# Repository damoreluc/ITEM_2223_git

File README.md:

# ITEM_2223_git
Repository progetti hardware con Autodesk Eagle di ITEM 2022-2023

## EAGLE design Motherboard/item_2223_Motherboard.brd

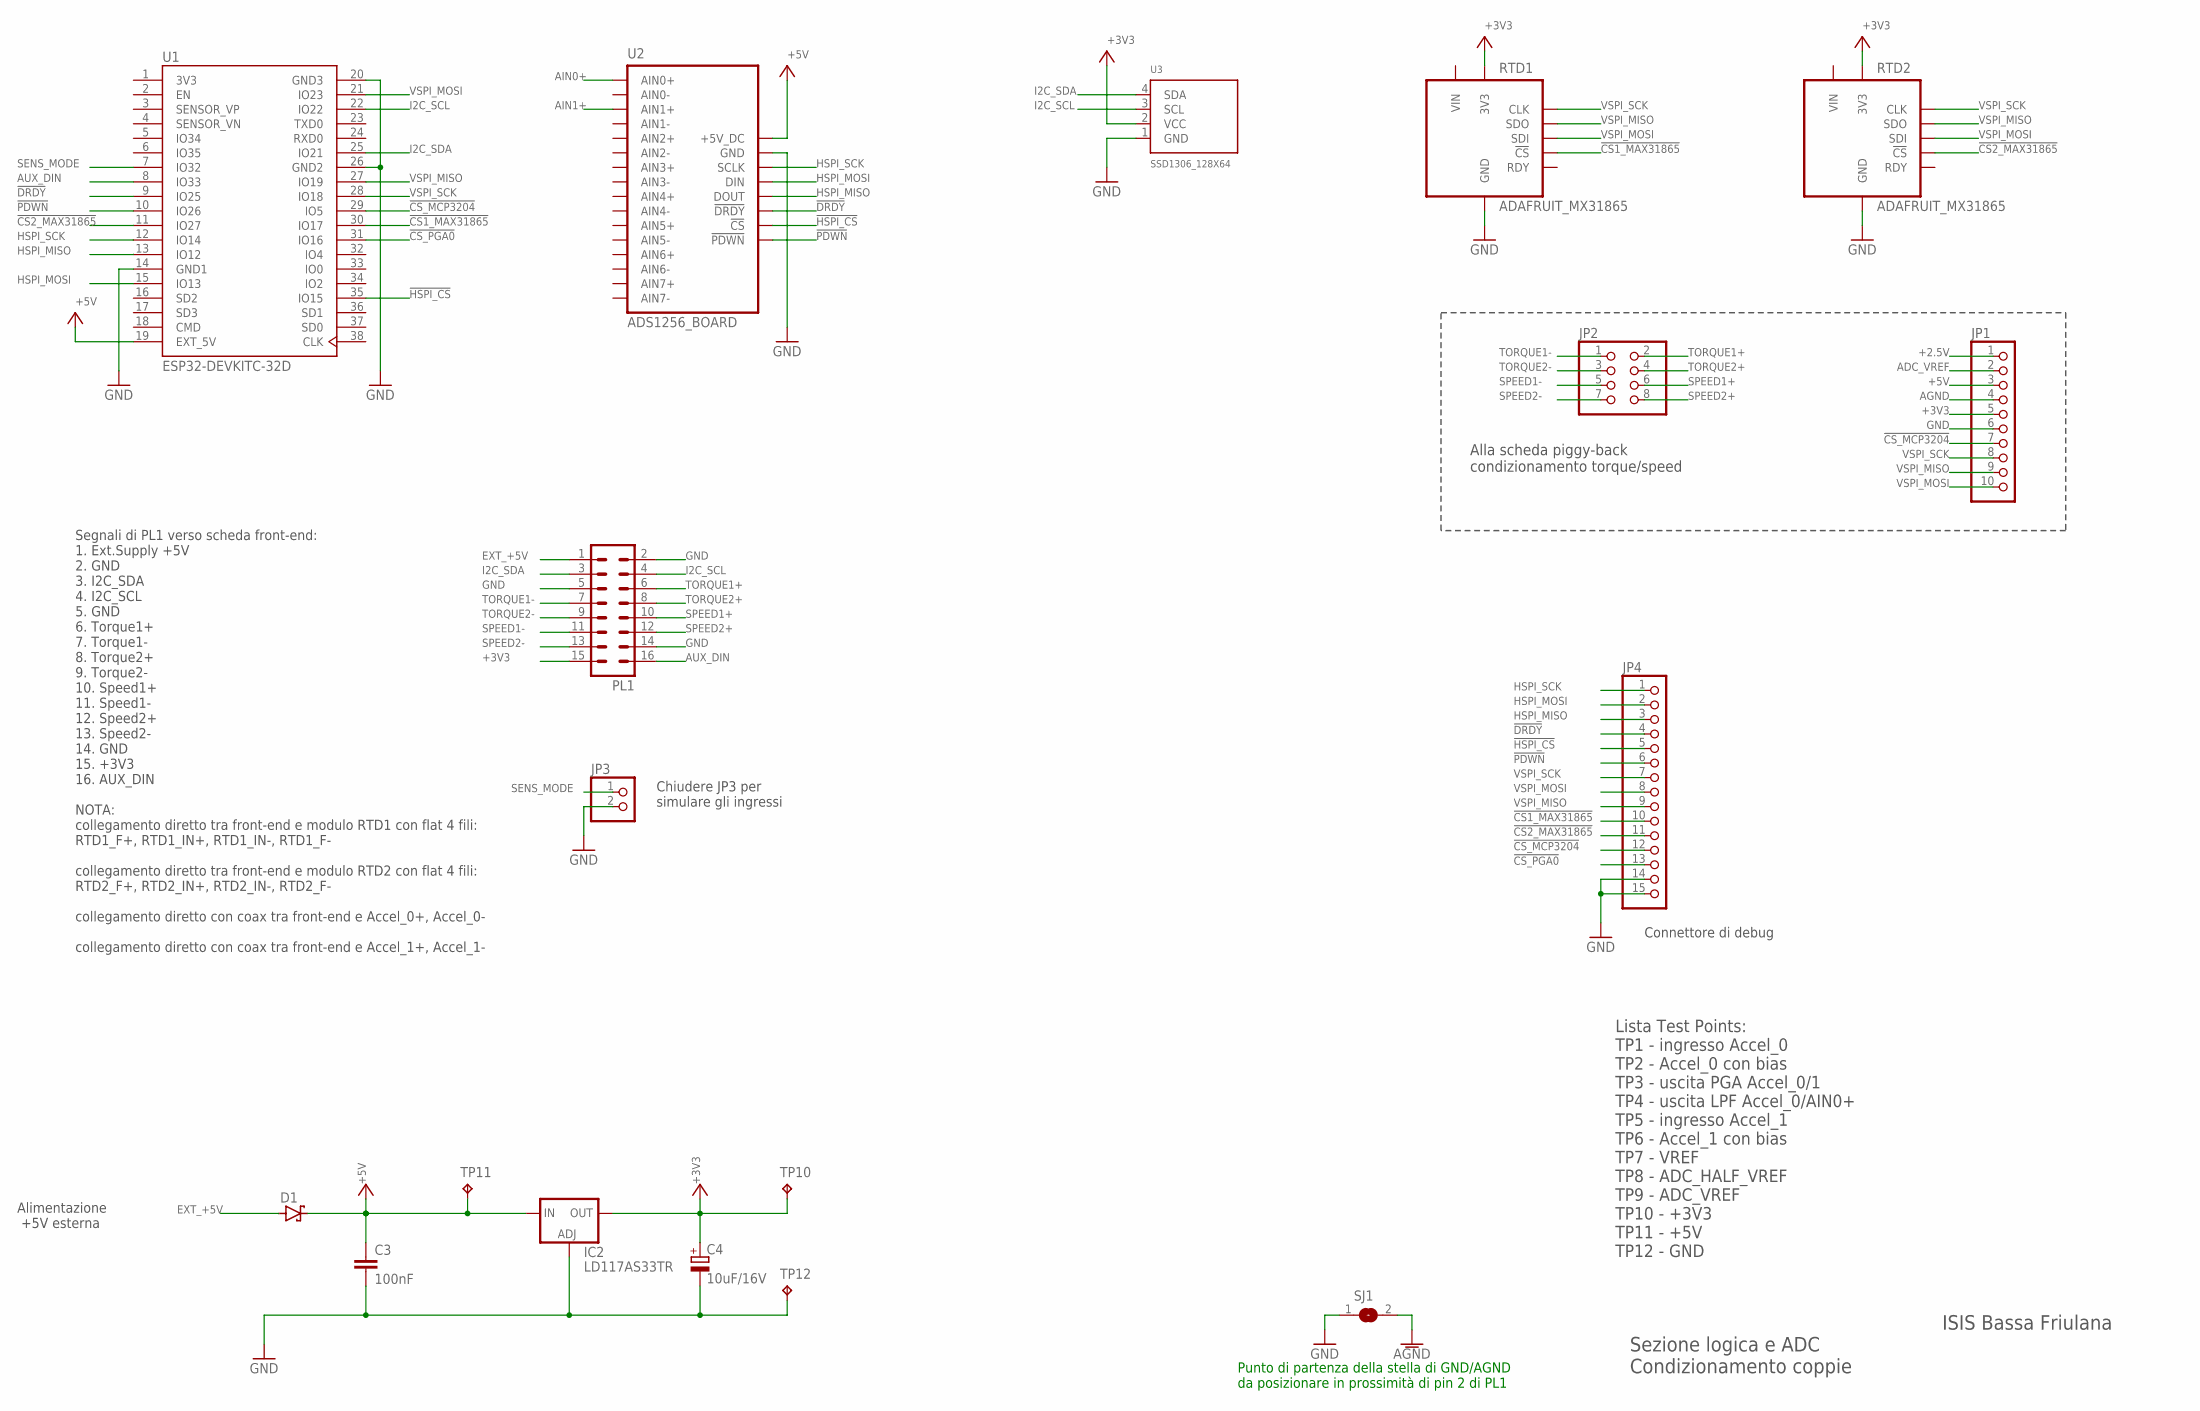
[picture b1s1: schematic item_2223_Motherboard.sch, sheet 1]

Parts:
C3: 100nF; C0805K
C4: 10uF/16V; E3,5-8
D1: SCHOTTKY-DIODEDO35-7; DO35-7
IC2: LD117AS33TR; SOT223
JP1: PINHD-1X10; 1X10
JP2: PINHD-2X4; 2X04
JP3: PINHD-1X2; 1X02
JP4: PINHD-1X15; 1X15
PL1: 16H
RTD1, RTD2: ADAFRUIT_MX31865; ADAFRUIT_MAX31865
SJ1: SJ
TP10, TP11: TPTP16SQ; TP16SQ
TP12: TPTP14R; TP14R
U1: ESP32-DEVKITC-32D; MODULE_ESP32-DEVKITC-32D
U2: ADS1256_BOARD
U3: SSD1306_128X64; 128X64

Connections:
3V3: U1.1 (3V3)
!CS1_MAX31865!: JP4.10, RTD1.P7 (!CS!), U1.30 (IO17)
!CS2_MAX31865!: JP4.11, RTD2.P7 (!CS!), U1.11 (IO27)
!CS_MCP3204!: JP1.7, JP4.12, U1.29 (IO5)
!CS_PGA0!: JP4.13, U1.31 (IO16); also elsewhere on the board
!DRDY!: JP4.4, U1.9 (IO25), U2.!DRDY!
!HSPI_CS!: JP4.5, U1.35 (IO15), U2.!CS!
!PDWN!: JP4.6, U1.10 (IO26), U2.PDWN (!PDWN!)
+2.5V: JP1.1; also elsewhere on the board
+3V3: C4.+, IC2.4 (OUT), JP1.5, PL1.15, RTD1.P3 (3V3), RTD2.P3 (3V3), TP10.TP, U3.2 (VCC); also elsewhere on the board
+5V: C3.1, D1.C, IC2.3 (IN), JP1.3, TP11.TP, U1.19 (EXT_5V), U2.5V_DC (+5V_DC); also elsewhere on the board
ADC_VREF: JP1.2; also elsewhere on the board
AGND: JP1.4, SJ1.2; also elsewhere on the board
AIN0+: U2.AIN0+; also elsewhere on the board
AIN1+: U2.AIN1+; also elsewhere on the board
AUX_DIN: PL1.16, U1.8 (IO33)
EXT_+5V: D1.A, PL1.1
GND: C3.2, C4.-, IC2.1 (ADJ), JP1.6, JP3.2, JP4.14, JP4.15, PL1.2, PL1.5, PL1.14, RTD1.P2 (GND), RTD2.P2 (GND), SJ1.1, TP12.TP, U1.14 (GND1), U1.20 (GND3), U1.26 (GND2), U2.GND, U3.1 (GND); also elsewhere on the board
HSPI_MISO: JP4.3, U1.13 (IO12), U2.DOUT
HSPI_MOSI: JP4.2, U1.15 (IO13), U2.DIN
HSPI_SCK: JP4.1, U1.12 (IO14), U2.SCLK
I2C_SCL: PL1.4, U1.22 (IO22), U3.3 (SCL)
I2C_SDA: PL1.3, U1.25 (IO21), U3.4 (SDA)
SENS_MODE: JP3.1, U1.7 (IO32)
SPEED1+: JP2.6, PL1.10
SPEED1-: JP2.5, PL1.11
SPEED2+: JP2.8, PL1.12
SPEED2-: JP2.7, PL1.13
TORQUE1+: JP2.2, PL1.6
TORQUE1-: JP2.1, PL1.7
TORQUE2+: JP2.4, PL1.8
TORQUE2-: JP2.3, PL1.9
VIN: RTD1.P1 (VIN), RTD2.P1 (VIN)
VSPI_MISO: JP1.9, JP4.9, RTD1.P5 (SDO), RTD2.P5 (SDO), U1.27 (IO19)
VSPI_MOSI: JP1.10, JP4.8, RTD1.P6 (SDI), RTD2.P6 (SDI), U1.21 (IO23); also elsewhere on the board
VSPI_SCK: JP1.8, JP4.7, RTD1.P4 (CLK), RTD2.P4 (CLK), U1.28 (IO18); also elsewhere on the board

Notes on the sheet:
Sezione logica e ADC Condizionamento coppie
ISIS Bassa Friulana
Lista Test Points: TP1 - ingresso Accel_0 TP2 - Accel_0 con bias TP3 - uscita PGA Accel_0/1 TP4 - uscita LPF Accel_0/AIN0+ TP5 - ingresso Accel_1 TP6 - Accel_1 con bias TP7 - VREF TP8 - ADC_HALF_VREF TP9 - ADC_VREF TP10 - +3V3 TP11 - +5V TP12 - GND
Alla scheda piggy-back condizionamento torque/speed
Segnali di PL1 verso scheda front-end: 1. Ext.Supply +5V 2. GND 3. I2C_SDA 4. I2C_SCL 5. GND 6. Torque1+ 7. Torque1- 8. Torque2+ 9. Torque2- 10. Speed1+ 11. Speed1- 12. Speed2+ 13. Speed2- 14. GND 15. +3V3 16. AUX_DIN NOTA: collegamento diretto tra front-end e modulo RTD1 con flat 4 fili: RTD1_F+, 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
Alimentazione +5V esterna
Chiudere JP3 per simulare gli ingressi
Connettore di debug
Punto di partenza della stella di GND/AGND da posizionare in prossimità di pin 2 di PL1

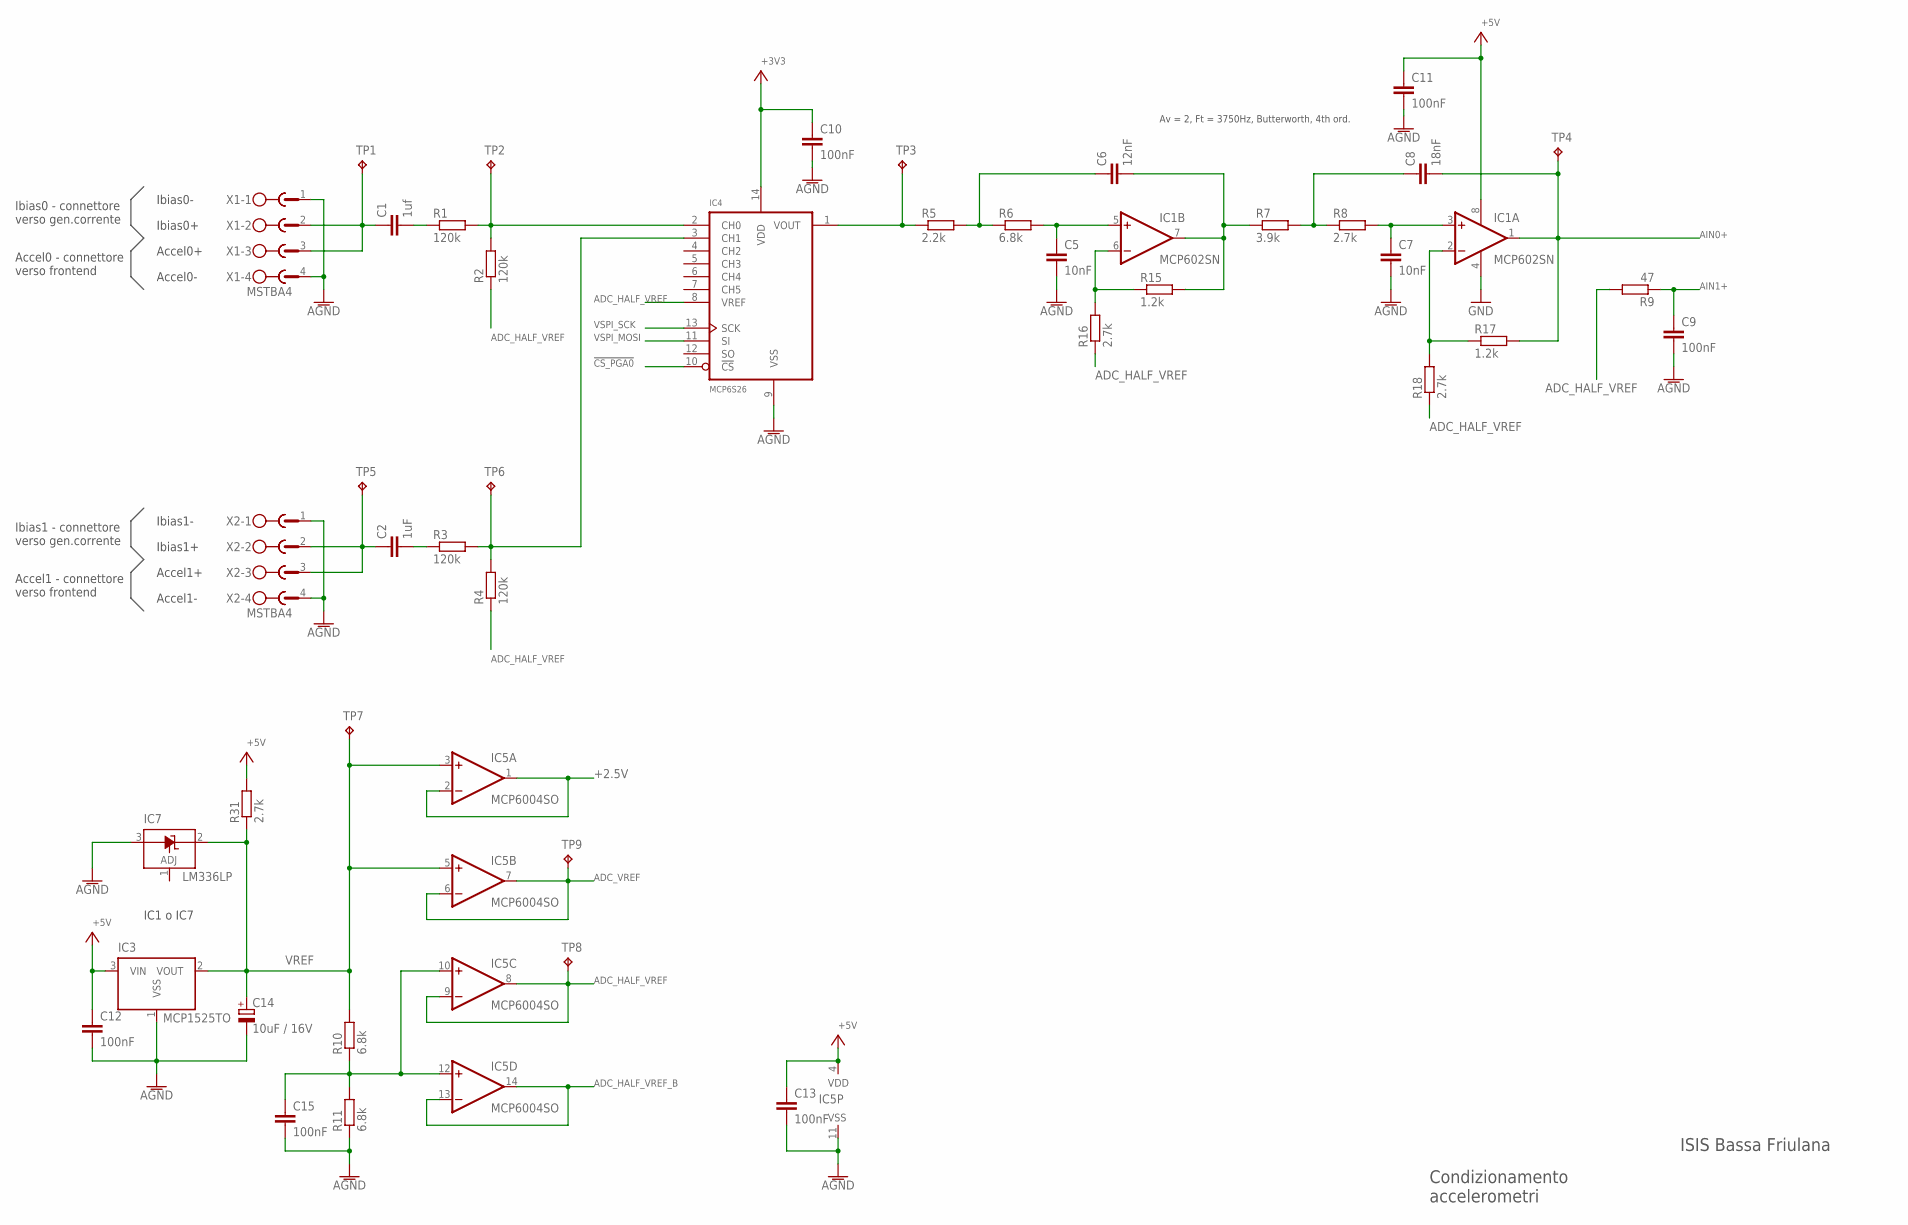
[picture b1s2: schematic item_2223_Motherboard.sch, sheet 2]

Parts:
C1: 1uf; C1206
C2: 1uF; C1206
C5, C7: 10nF; C0805K
C6: 12nF; C0805K
C8: 18nF; C0805K
C9, C10, C11: 100nF; C0805K
C12, C13, C15: 100nF; C0805
C14: 10uF / 16V; PANASONIC_C
IC1: MCP602SN; SO08
IC3: MCP1525TO; TO92
IC4: MCP6S26; SO14
IC5: MCP6004SO; SO14
IC7: LM336LP; TO92
R1, R2, R3, R4: 120k; R0805
R5: 2.2k; R0805
R6, R10, R11: 6.8k; R0805
R7: 3.9k; R0805
R8, R16, R18, R31: 2.7k; R0805
R9: 47; R0805
R15, R17: 1.2k; R0805
TP1, TP2, TP3, TP4, TP5, TP6: TPTP14R; TP14R
TP7, TP8: TPTP16R; TP16R
TP9: TPTP16SQ; TP16SQ
X1, X2: MSTBA4

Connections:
!CS_PGA0!: IC4.10 (!CS!); also elsewhere on the board
+2.5V: IC5.1 (OUT), IC5.2 (-IN); also elsewhere on the board
+3V3: C10.1, IC4.14 (VDD); also elsewhere on the board
+5V: C11.1, C12.1, C13.1, IC1.8 (V+), IC3.3 (VIN), IC5.4 (VDD), R31.2; also elsewhere on the board
ADC_HALF_VREF: IC4.8 (VREF), IC5.8 (OUT), IC5.9 (-IN), R2.1, R4.1, R9.2, R16.1, R18.1, TP8.TP
ADC_HALF_VREF_B: IC5.13 (-IN), IC5.14 (OUT)
ADC_VREF: IC5.6 (-IN), IC5.7 (OUT), TP9.TP; also elsewhere on the board
AGND: C5.2, C7.2, C9.2, C10.2, C11.2, C12.2, C13.2, C14.-, C15.2, IC3.1 (VSS), IC4.9 (VSS), IC5.11 (VSS), IC7.3 (A), R11.1, X1.1, X1.4, X2.1, X2.4; also elsewhere on the board
AIN0+: C8.2, IC1.1 (OUT), R17.2, TP4.TP; also elsewhere on the board
AIN1+: C9.1, R9.1; also elsewhere on the board
GND: IC1.4 (V-); also elsewhere on the board
unnamed: C15.1, IC5.10 (+IN), IC5.12 (+IN), R10.1, R11.2
unnamed: C1.1, TP1.TP, X1.2, X1.3
unnamed: C2.1, TP5.TP, X2.2, X2.3
unnamed: IC4.2 (CH0), R1.2, R2.2, TP2.TP
unnamed: IC4.1 (VOUT), R5.1, TP3.TP
unnamed: C1.2, R1.1
unnamed: C2.2, R3.1
unnamed: IC1.6 (-IN), R15.1, R16.2
unnamed: C6.1, R5.2, R6.1
unnamed: C5.1, IC1.5 (+IN), R6.2
unnamed: C6.2, IC1.7 (OUT), R7.1, R15.2
unnamed: C8.1, R7.2, R8.1
unnamed: C7.1, IC1.3 (+IN), R8.2
unnamed: IC4.3 (CH1), R3.2, R4.2, TP6.TP
unnamed: IC1.2 (-IN), R17.1, R18.2
VREF: C14.+, IC3.2 (VOUT), IC5.3 (+IN), IC5.5 (+IN), IC7.2 (C), R10.2, R31.1, TP7.TP
VSPI_MOSI: IC4.11 (SI); also elsewhere on the board
VSPI_SCK: IC4.13 (SCK); also elsewhere on the board

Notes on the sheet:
Condizionamento accelerometri
ISIS Bassa Friulana
Av = 2, Ft = 3750Hz, Butterworth, 4th ord.
Accel0 - connettore verso frontend
Accel0+
Accel0-
Ibias0 - connettore verso gen.corrente
Ibias0-
Ibias0+
Accel1 - connettore verso frontend
Accel1+
Accel1-
Ibias1 - connettore verso gen.corrente
Ibias1-
Ibias1+
IC1 o IC7

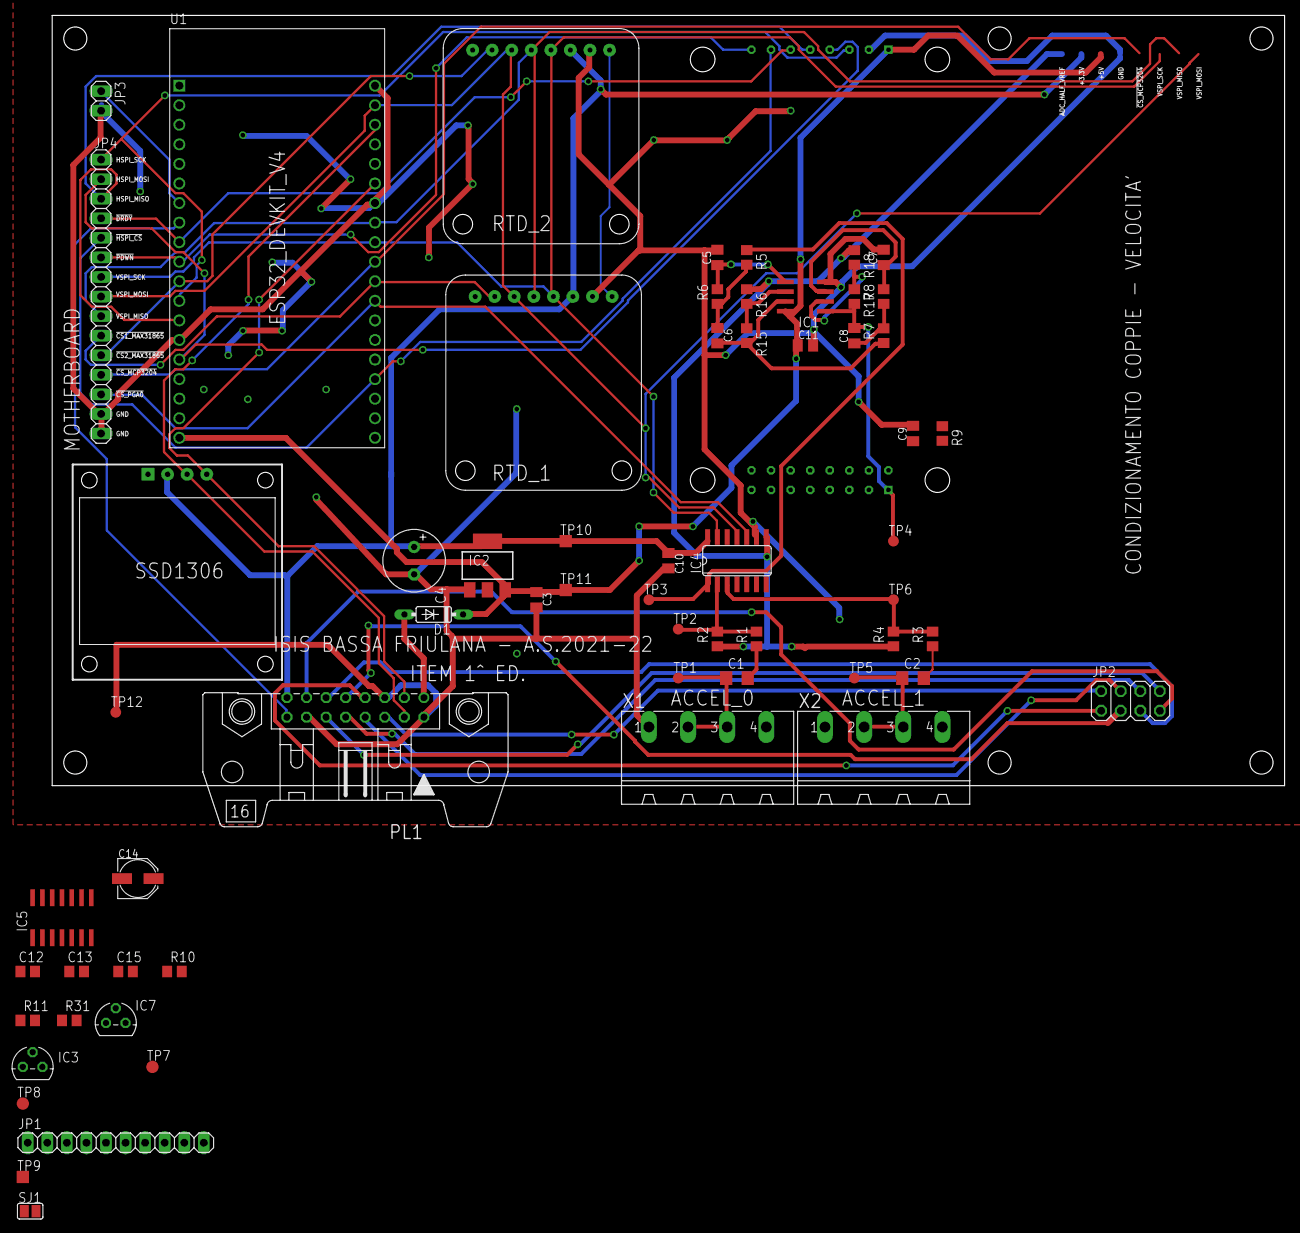
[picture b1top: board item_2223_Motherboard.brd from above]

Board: 2 copper layers, 160.0 x 100.0 mm, 63 parts (1 on the bottom side), 53 nets.

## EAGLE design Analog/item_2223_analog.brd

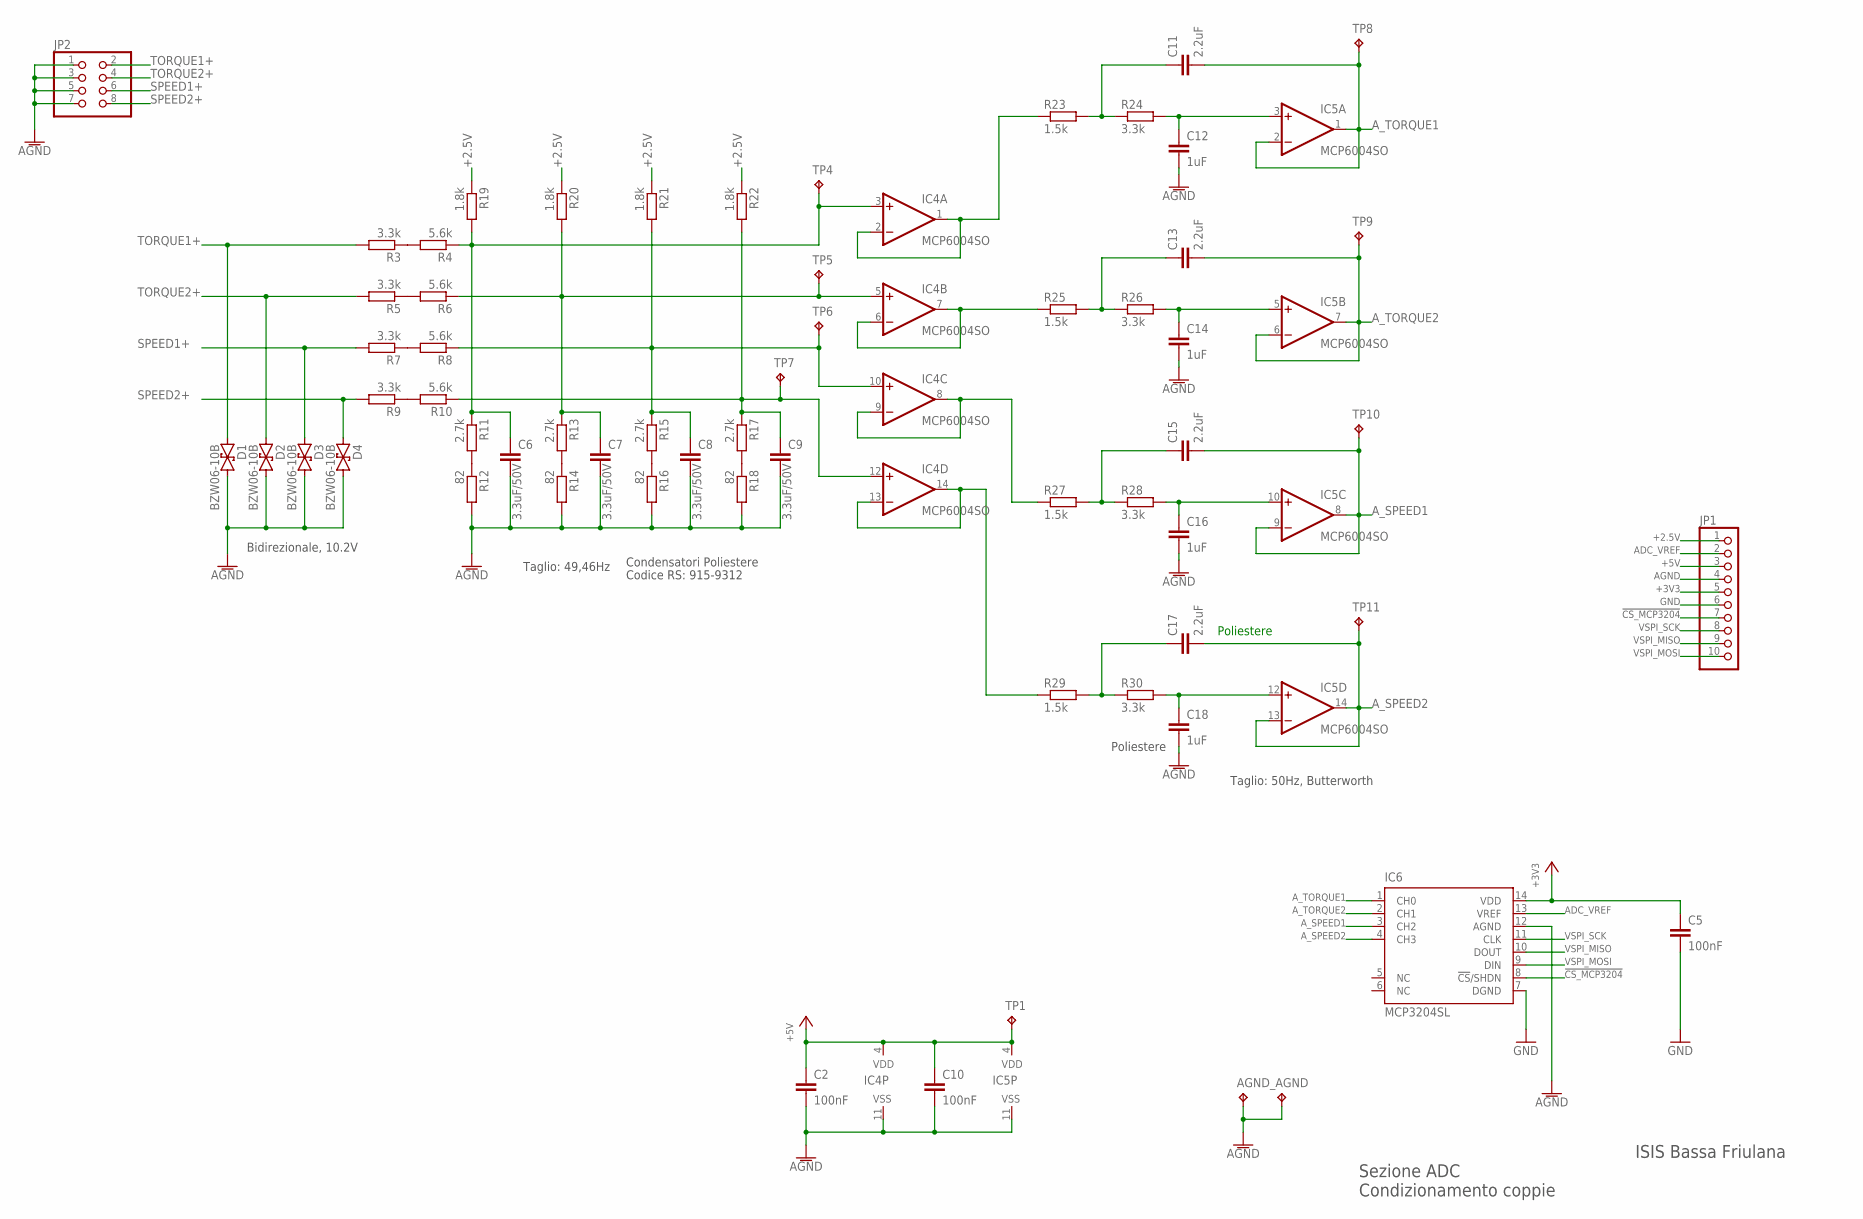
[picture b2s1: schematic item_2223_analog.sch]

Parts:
AGND: TPTP18SQ; TP18SQ
AGND_: TPTP18SQ; TP18SQ
C2, C5, C10: 100nF; C0805
C6, C7, C8, C9: 3.3uF/50V; C0805
C11, C13, C15, C17: 2.2uF; C0805
C12, C14, C16, C18: 1uF; C0805
D1, D2, D3, D4: BZW06-10B; F126Z12
IC4, IC5: MCP6004SO; SO14
IC6: MCP3204SL; SO14
JP1: PINHD-1X10; 1X10
JP2: PINHD-2X4; 2X04
R3, R5, R9, R24, R26, R28, R30: 3.3k; R0805
R4, R6, R8, R10: 5.6k; R0805
R7: 3.3k; M0805
R11, R13, R15, R17: 2.7k; R0805
R12, R14, R16, R18: 82; R0805
R19, R20, R21, R22: 1.8k; R0805
R23, R25, R27, R29: 1.5k; R0805
TP1: TPTP16R; TP16R
TP4, TP5, TP6, TP7, TP8, TP9, TP10, TP11: TPTP14R; TP14R

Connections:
!CS_MCP3204!: IC6.8 (!CS!/SHDN), JP1.7
+2.5V: JP1.1, R19.1, R20.1, R21.1, R22.1
+3V3: C5.1, IC6.14 (VDD), JP1.5
+5V: C2.1, C10.1, IC4.4 (VDD), IC5.4 (VDD), JP1.3, TP1.TP
ADC_VREF: IC6.13 (VREF), JP1.2
AGND: AGND.TP, AGND_.TP, C2.2, C6.2, C7.2, C8.2, C9.2, C10.2, C12.2, C14.2, C16.2, C18.2, D1.C (2), D2.C (2), D3.C (2), D4.C (2), IC4.11 (VSS), IC5.11 (VSS), IC6.12 (AGND), JP1.4, JP2.1, JP2.3, JP2.5, JP2.7, R12.2, R14.2, R16.2, R18.2
A_SPEED1: C15.2, IC5.8 (OUT), IC5.9 (-IN), IC6.3 (CH2), TP10.TP
A_SPEED2: C17.2, IC5.13 (-IN), IC5.14 (OUT), IC6.4 (CH3), TP11.TP
A_TORQUE1: C11.2, IC5.1 (OUT), IC5.2 (-IN), IC6.1 (CH0), TP8.TP
A_TORQUE2: C13.2, IC5.6 (-IN), IC5.7 (OUT), IC6.2 (CH1), TP9.TP
GND: C5.2, IC6.7 (DGND), JP1.6
unnamed: R3.1, R4.2
unnamed: R5.1, R6.2
unnamed: R7.1, R8.2
unnamed: R9.1, R10.2
unnamed: R11.2, R12.1
unnamed: C6.1, IC4.3 (+IN), R4.1, R11.1, R19.2, TP4.TP
unnamed: R13.2, R14.1
unnamed: R15.2, R16.1
unnamed: R17.2, R18.1
unnamed: C7.1, IC4.5 (+IN), R6.1, R13.1, R20.2, TP5.TP
unnamed: C8.1, IC4.10 (+IN), R8.1, R15.1, R21.2, TP6.TP
unnamed: C9.1, IC4.12 (+IN), R10.1, R17.1, R22.2, TP7.TP
unnamed: IC4.1 (OUT), IC4.2 (-IN), R23.1
unnamed: IC4.6 (-IN), IC4.7 (OUT), R25.1
unnamed: IC4.8 (OUT), IC4.9 (-IN), R27.1
unnamed: IC4.13 (-IN), IC4.14 (OUT), R29.1
unnamed: C11.1, R23.2, R24.1
unnamed: C12.1, IC5.3 (+IN), R24.2
unnamed: C13.1, R25.2, R26.1
unnamed: C14.1, IC5.5 (+IN), R26.2
unnamed: C15.1, R27.2, R28.1
unnamed: C16.1, IC5.10 (+IN), R28.2
unnamed: C17.1, R29.2, R30.1
unnamed: C18.1, IC5.12 (+IN), R30.2
SPEED1+: D3.A (1), JP2.6, R7.2
SPEED2+: D4.A (1), JP2.8, R9.2
TORQUE1+: D1.A (1), JP2.2, R3.2
TORQUE2+: D2.A (1), JP2.4, R5.2
VSPI_MISO: IC6.10 (DOUT), JP1.9
VSPI_MOSI: IC6.9 (DIN), JP1.10
VSPI_SCK: IC6.11 (CLK), JP1.8

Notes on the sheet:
Sezione ADC Condizionamento coppie
ISIS Bassa Friulana
Condensatori Poliestere
Taglio: 50Hz, Butterworth
Poliestere
Taglio: 49,46Hz
Bidirezionale, 10.2V
Codice RS: 915-9312

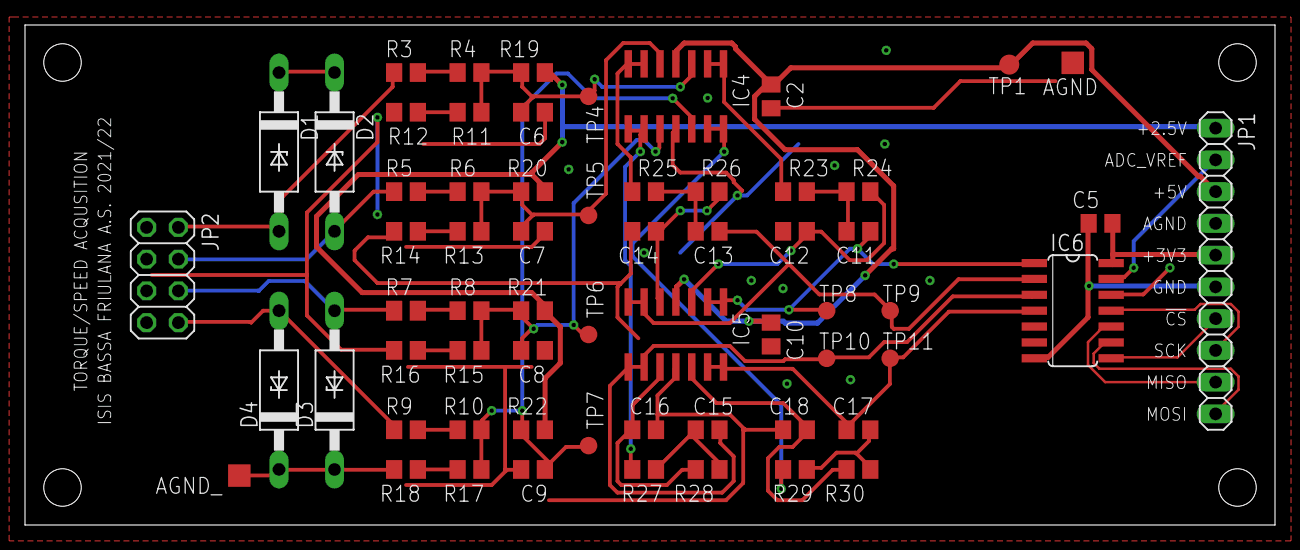
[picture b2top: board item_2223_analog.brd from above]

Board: 2 copper layers, 100.0 x 40.0 mm, 63 parts (0 on the bottom side), 42 nets.

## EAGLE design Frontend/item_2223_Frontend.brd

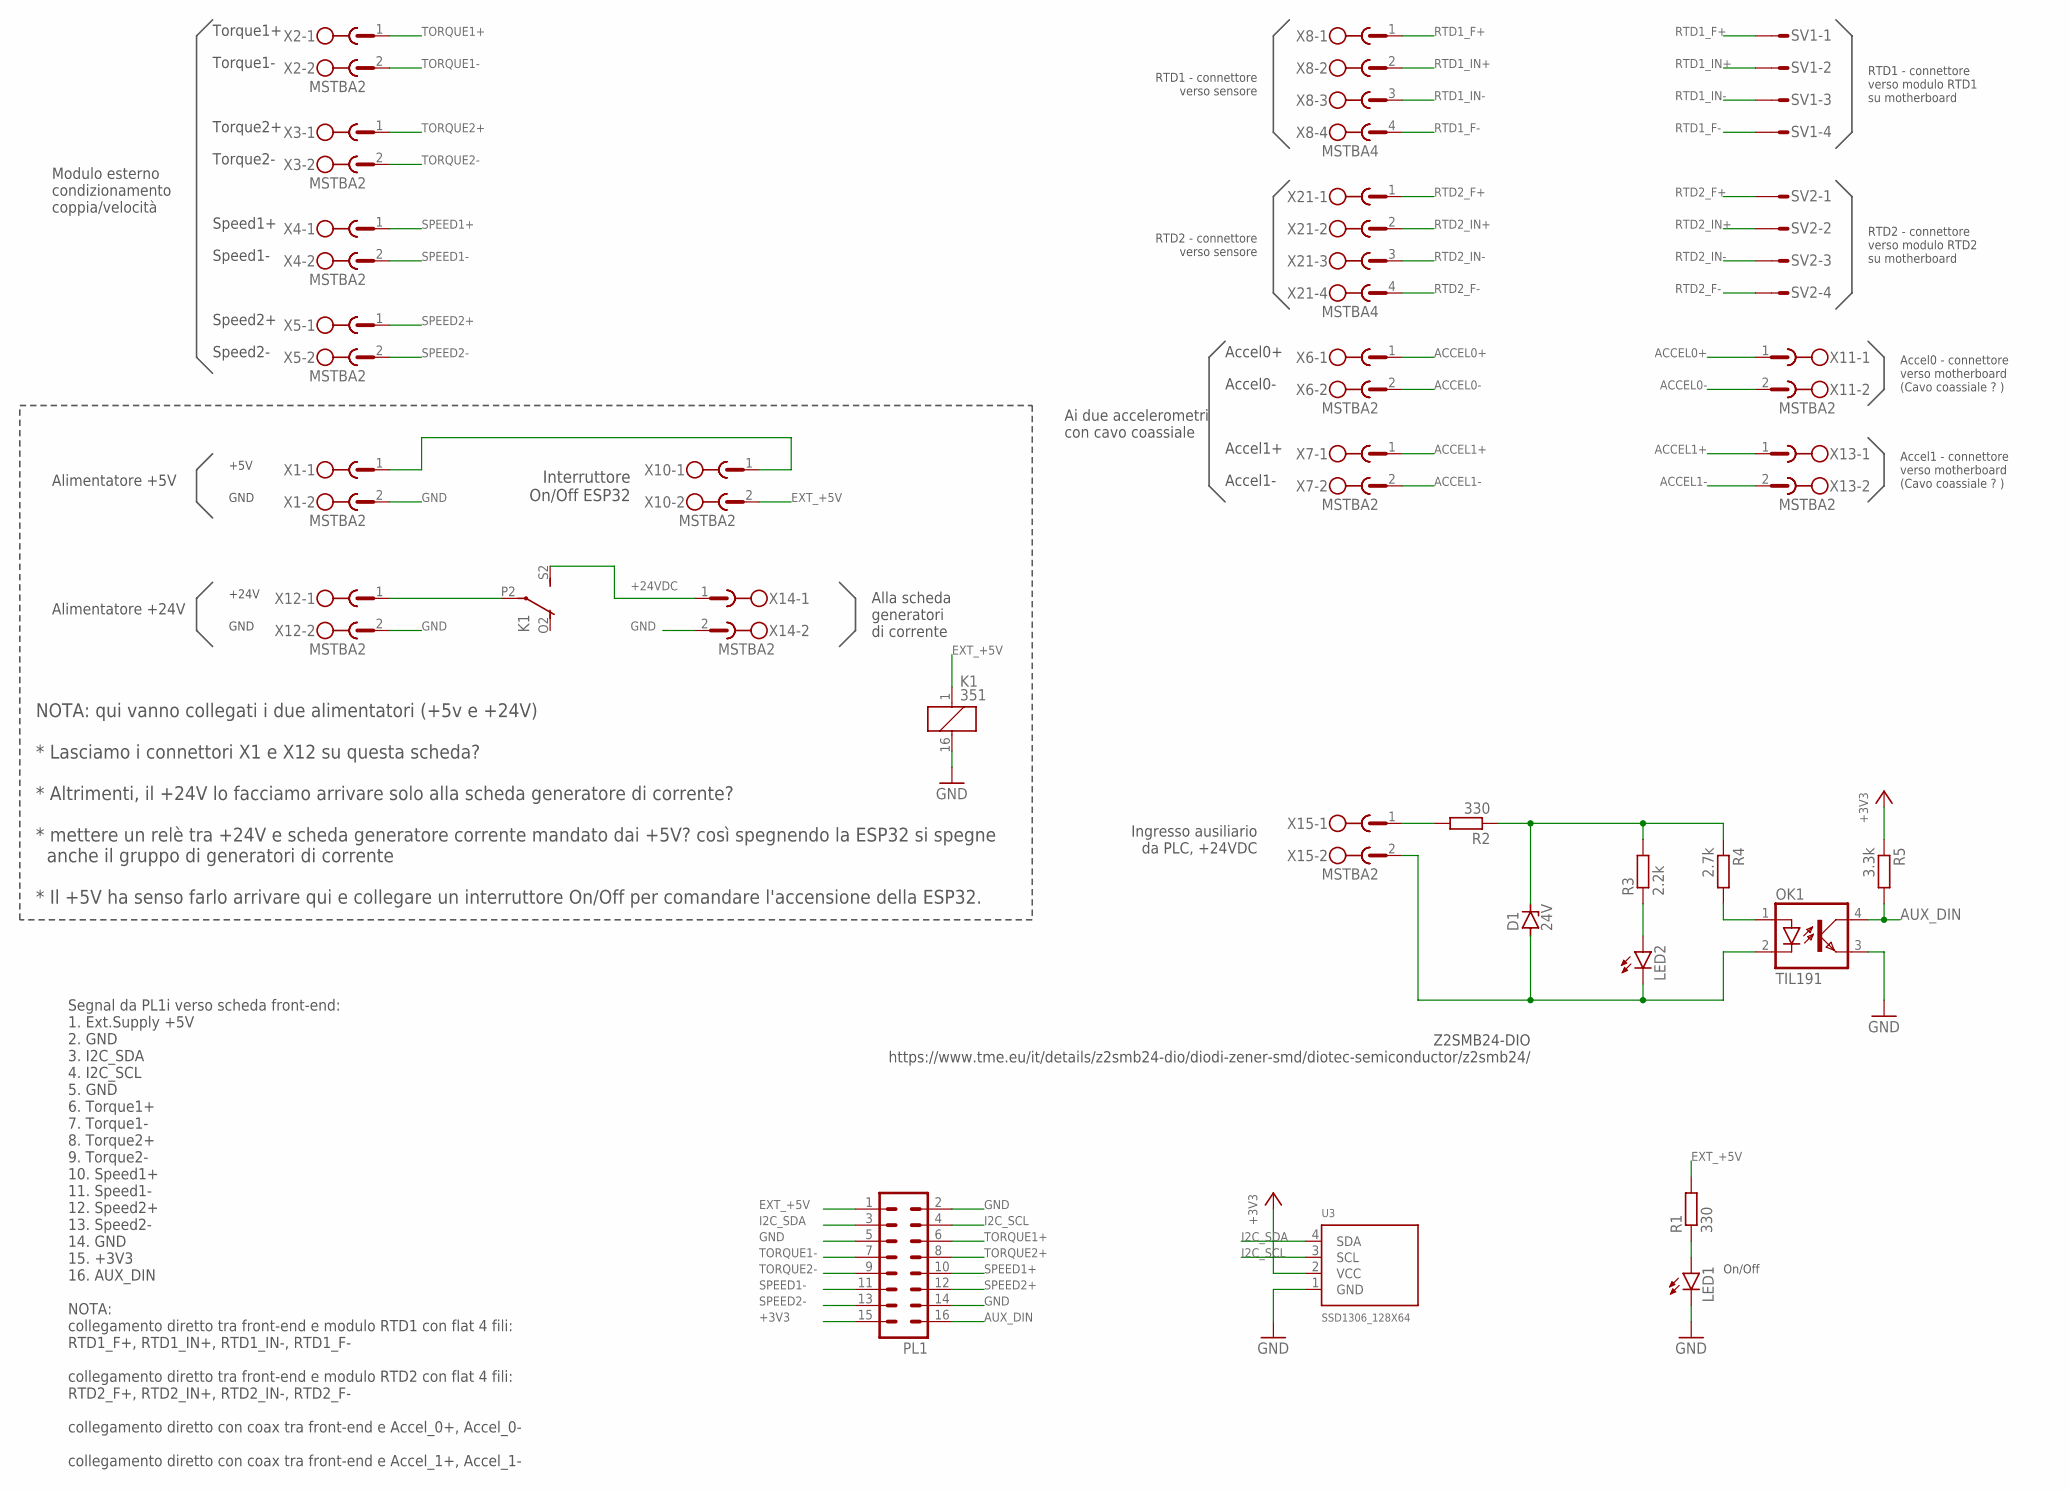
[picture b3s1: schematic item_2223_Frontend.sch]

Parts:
D1: 24V; SMB
K1: 351
LED1, LED2: LED5MM
OK1: TIL191; DIL04
PL1: 16H
R1, R2: 330; R0805
R3: 2.2k; R0805
R4: 2.7k; R0805
R5: 3.3k; R0805
SV1, SV2: S04P
U3: SSD1306_128X64; 128X64
X1, X2, X3, X4, X5, X6, X7, X10, X11, X12, X13, X14, X15: MSTBA2
X8, X21: MSTBA4

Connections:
+3V3: PL1.15, R5.1, U3.2 (VCC)
+24VDC: K1.S2 (S), X14.1
ACCEL0+: X6.1, X11.1
ACCEL0-: X6.2, X11.2
ACCEL1+: X7.1, X13.1
ACCEL1-: X7.2, X13.2
AUX_DIN: OK1.4 (COL), PL1.16, R5.2
EXT_+5V: K1.1, PL1.1, R1.2, X10.2
GND: K1.16 (2), LED1.K (C), OK1.3 (EMIT), PL1.2, PL1.5, PL1.14, U3.1 (GND), X1.2, X12.2, X14.2
I2C_SCL: PL1.4, U3.3 (SCL)
I2C_SDA: PL1.3, U3.4 (SDA)
unnamed: R2.2, X15.1
unnamed: X1.1, X10.1
unnamed: LED1.A, R1.1
unnamed: D1.C, R2.1, R3.2, R4.1
unnamed: D1.A, LED2.K (C), OK1.2 (C), X15.2
unnamed: K1.P2, X12.1
unnamed: LED2.A, R3.1
unnamed: OK1.1 (A), R4.2
RTD1_F+: SV1.1, X8.1
RTD1_F-: SV1.4, X8.4
RTD1_IN+: SV1.2, X8.2
RTD1_IN-: SV1.3, X8.3
RTD2_F+: SV2.1, X21.1
RTD2_F-: SV2.4, X21.4
RTD2_IN+: SV2.2, X21.2
RTD2_IN-: SV2.3, X21.3
SPEED1+: PL1.10, X4.1
SPEED1-: PL1.11, X4.2
SPEED2+: PL1.12, X5.1
SPEED2-: PL1.13, X5.2
TORQUE1+: PL1.6, X2.1
TORQUE1-: PL1.7, X2.2
TORQUE2+: PL1.8, X3.1
TORQUE2-: PL1.9, X3.2

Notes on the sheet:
Segnal da PL1i verso scheda front-end: 1. Ext.Supply +5V 2. GND 3. I2C_SDA 4. I2C_SCL 5. GND 6. Torque1+ 7. Torque1- 8. Torque2+ 9. Torque2- 10. Speed1+ 11. Speed1- 12. Speed2+ 13. Speed2- 14. GND 15. +3V3 16. AUX_DIN NOTA: collegamento diretto tra front-end e modulo RTD1 con flat 4 fili: RTD1_F+, 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
Interruttore On/Off ESP32
Alimentatore +5V
+5V
GND
Torque1+
Torque1-
Torque2+
Torque2-
Speed1+
Speed1-
Speed2+
Speed2-
Accel0+
Accel0-
Accel1+
Accel1-
RTD1 - connettore verso sensore
RTD2 - connettore verso sensore
RTD1 - connettore verso modulo RTD1 su motherboard
RTD2 - connettore verso modulo RTD2 su motherboard
Ai due accelerometri con cavo coassiale
Modulo esterno condizionamento coppia/velocità
Alimentatore +24V
+24V
Accel0 - connettore verso motherboard (Cavo coassiale ? )
Accel1 - connettore verso motherboard (Cavo coassiale ? )
NOTA: qui vanno collegati i due alimentatori (+5v e +24V) * Lasciamo i connettori X1 e X12 su questa scheda? * Altrimenti, il +24V lo facciamo arrivare solo alla scheda generatore di corrente? * mettere un relè tra +24V e scheda generatore corrente mandato dai +5V? così spegnendo la ESP32 si spegne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
On/Off
Alla scheda generatori di corrente
Ingresso ausiliario da PLC, +24VDC
Z2SMB24-DIO https://www.tme.eu/it/details/z2smb24-dio/diodi-zener-smd/diotec-semiconductor/z2smb24/

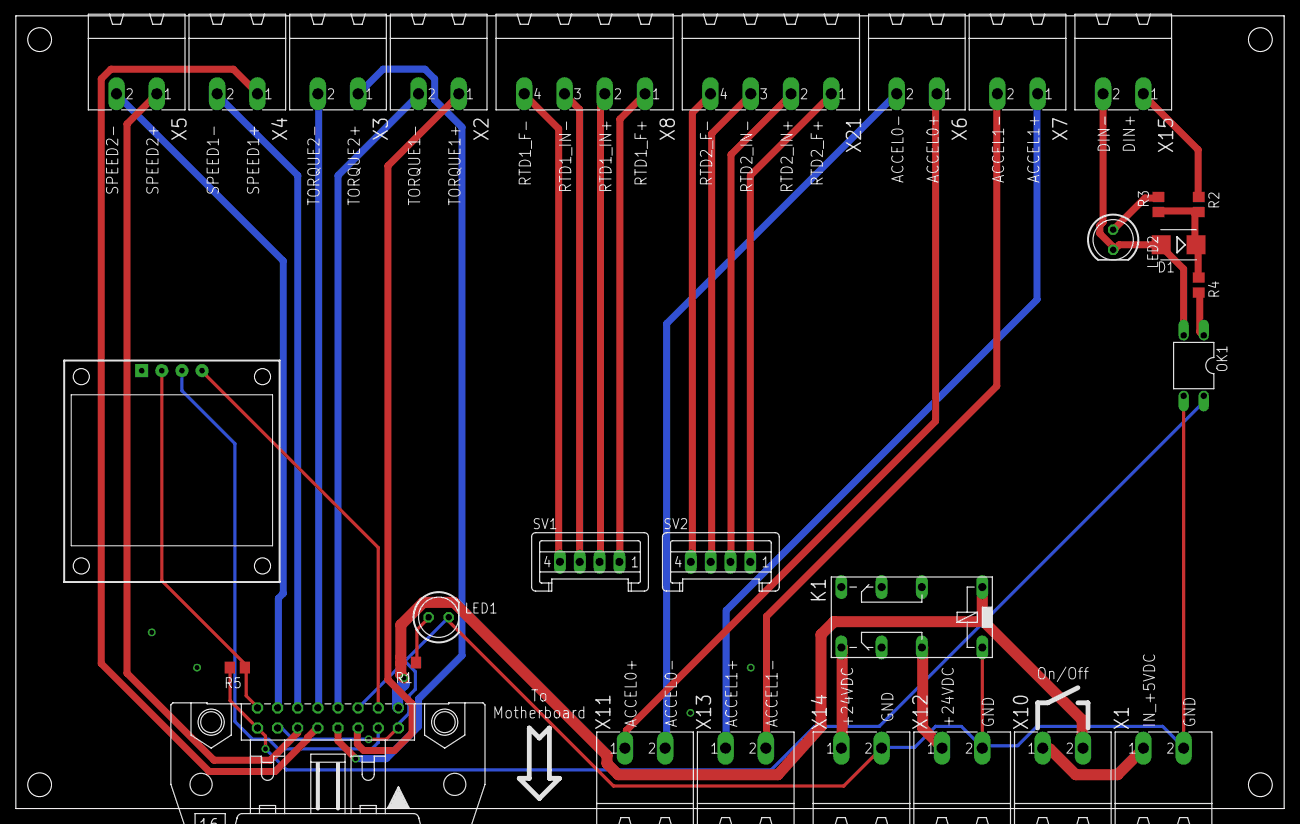
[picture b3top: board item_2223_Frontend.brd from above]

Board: 2 copper layers, 160.0 x 100.0 mm, 29 parts (0 on the bottom side), 35 nets.

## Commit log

2022-08-15 Versione iniziale
2022-08-15 Aggiungi pdf degli schematici
2022-08-15 Correggi errore tipografico in item_2223_Motherboard.sch
2022-10-05 Corretto GND di SSD1306 in Frontend e Motherboard
2022-11-18 ingresso differenziale e AGND
